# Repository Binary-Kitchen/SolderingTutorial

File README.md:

# Soldering Tutorial

This repository contains all files for our soldering kits and courses. Please feel free to download and use everything you need.

We've tried to collect and create tutorials with different difficulties and are offering SMD and DIP soldering kits.

For an overview of all kits with manuals and interactive pcb views go to: https://binary-kitchen.github.io/SolderingTutorial

### Linking directly to a kit

Every kit on the overview page has its own anchor, so you can link straight to its picture:
`https://binary-kitchen.github.io/SolderingTutorial/#Capybara` opens the page scrolled to the Capybara card and highlights it.
Clicking the small link icon on a card copies that deep link to your clipboard.

The overview page is generated from the project folders — `make landing_page`, i.e. `python build_landingpage.py`.
Every folder that contains a card image at `manual/images/thumbnail.{jpg,jpeg,png,gif,webp}` shows up automatically,
so a new kit only needs such a thumbnail to appear on the page.

If you want to buy soldering Kits you can find some here: [shop.blinkyparts.com](https://shop.blinkyparts.com)

We have tips how to organise a soldering workshop in the field and how to further decorate the kits: [Wiki: Festival Setup](https://github.com/Binary-Kitchen/SolderingTutorial/wiki/Festival-Setup)

## Soldering Kits

### [50 Ohm Dummy Load](50ohmDummyLoad/)

A simple Dummy Load for 50 Ohm made for every amateur radio operator.

- Difficulty: **§/5**

### [Atari Punk Console - STEAM Edition](AtariPunkConsoleSTEAM/)

One of the simplestes Synthesizers you can build. Only two NE555 make super cool sounds!

- Difficulty: **1/5**

### [ATX Breakout Board](ATXBreakoutBoardSMD/)

Handy Breakout Board to get all the important voltages from a standard ATX power supply.

- Difficulty: **4/5**

### [Al Hacka Alpaka](AlHackaAlpaka/)

Easy soldering kit in homage to Jugend hackt and its mascot.

### [Arrow SMD](ArrowSMD/)

Small soldering kit with an arrow on it from https://wiki.blinkenarea.org/index.php/AntiKippenLights-Mini.

- Difficulty: **4/5**

### [Axolotl Badge](AxolotlBadge/)

Easy RGB soldering kit with the best Axolotl!

- Difficulty: **2/5**

### [BleepBot](BleepBot/)

A talking robot!

- Difficulty: **2/5**

### [Blinkenrocket Mini](BlinkenrocketMini/)

A very simple soldering kit and a very intuitive way to program your own led matrix. Super fun blinkenrocket!

- Difficulty: **2/5**

### [BlinkyTree](BlinkyTree/)

The BlinkyTree is a soldering kit for a fantastic soldering Christmas tree. The great feature: By blowing on the tree, you can play different songs. A wonderful soldering kit for the Christmas season.

- Difficulty: **2/5**

### [Pooping Cat](PoopingCat/)

Can you please turn around? If you stare, the cat will stare back in all colours of the rainbow due to RGB-LEDs on the back. The soldering kit is very simple and easy to assemble.

- Difficulty: **2/5**

### [Cube DIP](CubeDIP/)

Simple LED cube consisting of 27 RGB LEDs in a 3x3x3 configuration. No programming needed.

- Difficulty: **3/5**

### [Daisy RGB](Daisy_RGB/)

This 3D construction kit allows you to solder a personalized daisy with a large RGB LED in the center, with colors adjustable using variable resistors and overall brightness and individual colors adjustable via slide switches.

- Difficulty: **2/5**

### [Dice DIP](DiceDIP/)

Electronic dice which uses button bouncing and timing for randomness.

- Difficulty: **3/5**

### [Dice Micro Controller DIP](DiceMcDIP/)

Dice with micro controller. Electronic dice which uses C random generator.

- Difficulty: **2/5**

### [Dino](Dino/)

This rainbow dinosaur will brighten up your life. The spikes are glowing in all colours of the rainbow due to RGB-LEDs on the back. The soldering kit is very simple and easy to assemble.

- Difficulty: **2/5**

### [Draussenfuchs Antenna](DraussenfuchsAntenne/)

A soldering kit for a simple 433MHz Yagi antenna designed for the draussenfuchs.de fox hunting game.

- Difficulty: **2/5**

### [Draussenfuchs Sender](DraussenfuchsSender/)

A soldering kit for a 433MHz fox sender for the draussenfuchs.de fox hunting game.

- Difficulty: **2/5**

### [Elefant](Elefant/)

Everyone knows the great elephant from the “Sendung mit der Maus” and, as always, he has a good idea. An LED in the trunk that lights up in RGB colors.

- Difficulty: **2/5**

### [Ermer Beeper DIP](ErmerBeeperDIP/)

The Ermer Beeper is a very neat continuity tester or beeper.

- Difficulty: **2/5**

### [Heartbeat](HeartbeatTHT/)

Small soldering kit with an heart and a beating led in the middle.

- Difficulty: **2/5**

### [Heart DIP](HeartDIP/)

Small soldering kit with an heart on from https://wiki.blinkenarea.org/index.php/AntiKippenLights-Atmel

- Difficulty: **2/5**

### [Heart SMD](HeartSMD/)

Small soldering kit with an heart on it from https://wiki.blinkenarea.org/index.php/AKL-Mini

- Difficulty: **4/5**

### [Humo - Solder-Fume Exctractor](Humo/)

This simple solder fume extractor just needs a PC fan and a solder fume filter. If you add some goggly eyes the fume extractor has a pretty nice smiling face. It is optimised for laser cut parts.

- Difficulty: **2/5**

### [I Can Solder DIP](ICanSolderDIP/)

Very easy soldering kit with three LEDs. Can be used as pin button.

- Difficulty: **1/5**

### [Katie The Cat](KatieTheCat/)

A wonderful and easy soldering Kit with two different eye-colours.

- Difficulty: **2/5**

### [Kitchen Head SMD](KitchenHeadSMD/)

Small soldering kit using SMD components with the kitchen head on it.

- Difficulty: **4/5**

### [LEDSchmuck](LEDSchmuck/)

The LED jewelry kit allows you to easily and quickly assemble earrings or pendants with RGB LEDs. It's a creative kit for making great individual jewelry pieces.

- Difficulty: **2/5**

### [LEDWolf](LEDWolf/)

This great LED wolf is a good way to start tinkering if you don't have a soldering iron with you at the moment. All you need is a little glue and a small Phillips screwdriver to assemble this great wolf.

- Difficulty: **1/5**

### [Maus](Maus/)

An easy hot wire soldering kit with the Sendung mit der Maus.

### [Moon Cat](MoonCat/)

Excuse me? What are you staring at? This wonderful kit is very simple in terms of circuitry, but the result is simply hilarious.

- Difficulty: **2/5**

### [Motörbörd](MotoerBoerd/)

Chirp chirp chirp, chirp chirp! The Motörbörd is a creative soldering kit that you can use to build your own little bird call generator. It is not powered by batteries, but by a small motor that generates electrical energy when turned like a dynamo.

- Difficulty: **2/5**

### [Mushroom Rocket](https://github.com/ventilator/soldering-mushroom-rocket/tree/main)

A fusion between a rocket and a mushroom

- Difficulty: **2/5**

### [NE555 Heart THT](NE555HeartTHT/)

A wonderful Heart with SMD LEDs. You can choose between full on, follow-LEDs and even can influence the speed of your LEDs.

- Difficulty: **3/5**

### [NE555 Heart SMD](NE555HeartSMD/)

A wonderful Heart with SMD LEDs. You can choose between full on, follow-LEDs and even can influence the speed of your LEDs.

- Difficulty: **4/5**

### [Nibble++](NibblePlusPlusSMD/)

A simple PCB to test your SMD hand-soldering skills. Going down to sand grain sized 01005 SMD parts, this button is a challenge for experienced "soldiers" and those who want to become one.

- Difficulty: **6/5**

### Nibble Peg DIP

#### [Nibble Peg DIP](NibblePegDIP/)

Very easy soldering Kit using simple Tools and nearly no soldering knowledge is needed.

- Difficulty: **1/5**

#### [Nibble Peg DIP with On/Off Switch](NibblePegDIPSwitch/)

Easy soldering Kit using simple Tools and nearly no soldering knowledge is needed.

- Difficulty: **2/5**

### [Nose Dog](NoseDog/)

Easy soldering Kit using simple Tools and nearly no soldering knowledge is needed.

- Difficulty: **2/5**

### [OpenDTU Breakout Board](OpenDTU_Breakout/)

A board to get information from your solar power panels with an Hoymiles inverter.

- Difficulty: **2/5**

### [Owl Thief THT](OwlThiefDIP/)

A simple joule thief circuit on the back of an owl. If you solder everything right, you can empty old batteries and make the eyes glow orange.

- Difficulty: **2/5**

### [Pinecil Case](Pinecil_Case/)

A perfect 3D-printed rugged case for your pinecil, extra tips and usb-c cable.

- Difficulty: **1/5**

### [Push-It DIP](PushItDIP/)

Simon Says clone with (optional) multiplayer mode

- Difficulty: **2/5**

### [Rainbow Butterfly](RainbowButterfly/)

A wonderful rainbow Butterfly. The wings are enlighted by RGB-LEDs from the back of the PCB. The soldering kit is very simple and easy to assemble.

- Difficulty: **2/5**

### [Rainbow Unicorn 1](RainbowUnicorn01/)

This unicorn will brighten up your life. The hair is glowing in all colours of the rainbow due to RGB-LEDs on the back. The soldering kit is very simple and easy to assemble.

- Difficulty: **2/5**

### [Ring Light SMD](RingLightSMD/)

A simple SMD learning kit where a light chases around a circle.

- Difficulty: **4/5**

### [Robo Robin](RoboRobin/)

Light up this super easy Robot. It has RGB-LEDs as eyes.

- Difficulty: **1/5**

### [Rainbow Rocket](RocketBadge/)

Fly to the moon with this RGB rocket badge.

- Difficulty: **2/5**

### [Saw-Tooth Organ DIP](SawToothOrganDIP/)

Some Transistors creating a saw tooth wave enabling a very simple organ which you can play like a piano with a stylus.

- Difficulty: **2/5**

### [Shitty Robot](ShittyRobots/)

A very easy circuit to power a little robot with a vibration motor.

- Difficulty: **1/5**

### [SmartLED](SmartLED/)

Create a wonderful smart LED-Lamp you can control with you Smartphone.

- Difficulty: **4/5**

### [Smartphone Robot](SmartphoneRobot/)

A robot made out of an old smartphone. You can controll it by turning light on and off.

- Difficulty: **2/5**

### [SMD Cat](SMDCat/)

A Cat in a box easy SMD kit. Bright glowing LED-eyes are watching every step! With this soldering kit it is super easy to learn SMD soldering.

- Difficulty: **3/5**

### [Solarpunk Synthesizer](SolarpunkSynth/)

A very simple solarpunk Synthesizer based on a simple Schmitt Trigger. Create crazy sounds with this simple soldering kit.

- Difficulty: **2/5**

### [SolderBox](SolderBox/)

We have designed a soldering box for you that is extra small but still contains everything you need. The box offers space for a complete soldering working place and is still so small that four of the boxes fit into a small Euro box.

- Difficulty: **1/5**

### [SpaceEggs](SpaceEggs/)

The **Space Egg** is a fun and beginner-friendly **soldering kit** combined with **3D-printed components**. It features an interactive mechanism where turning the egg

- Difficulty: **2/5**

### [WeevilEye](WeevilEye/)

The kit is a very easy kit with push-through parts, which is explicitly aimed at beginners. Once assembled, the red LED “eyes” light up brighter or dimmer depending on how much light falls on the photo sensor.

- Difficulty: **2/5**

## License

This work is licensed under different licenses. Please see subfolders for details and LICENSE.md file in the top level directory for all used license files.

## Copyright and Authorship

Please consider README.md in sub-folders for the Copyright and Authorship of the specific project.

## Authors

Boards:

- Arne Rossius [arne@blinkenarea.org](mailto:arne@blinkenarea.org)
- Thomas Basler [noby@binary-kitchen.de](mailto:noby@binary-kitchen.de)
- Francesco Truzzi <http://truzzi.me>
- Timo Schindler <https://www.timoschindler.de>
- Thomas Schmid

TeX-Code:

- Marei Peischl [marei@binary-kitchen.de](mailto:marei@binary-kitchen.de) <https://github.com/TeXhackse>

Comic:

- Mitch Altmann <http://cornfieldelectronics.com>
- Jeff Keyzer <http://mightyohm.com/blog/>
- Andie Nordgren [andie.nordgren@gmail.com](mailto:andie.nordgren@gmail.com)

Manuals:

- Michael Pajewski
- Marei Peischl [marei@binary-kitchen.de](mailto:marei@binary-kitchen.de) <https://github.com/TeXhackse>
- Timo Schindler <https://www.timoschindler.de>
- Hannes <https://github.com/misamura>
- Mario Langhammer <https://github.com/Mallo321123>

Note: This list of authors can be incomplete. Please also consider the README.md in the sub-folders for authorship.

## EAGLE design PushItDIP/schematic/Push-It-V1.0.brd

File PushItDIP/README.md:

# Push-It DIP
Simon Says clone with (optional) multiplayer mode

- Status: **Complete**
- Difficulty: **2/5**

### Parts List

| Quantity | Name        | Description                        | Signing/Colorcode             |
|----------|-------------|------------------------------------|-------------------------------|
| 5        | R1 - R4, R6 | Resistor 220 Ohm                   | red - red - brown - gold      |
| 1        | R5          | Resistor 1 Kilo Ohm                | brown - black - red - gold    |
| 1        | R7          | Resistor 10 Kilo Ohm               | brown - black - orange - gold |
| 7        | S1 - S7     | Button                             |                               |
| 1        | SG1         | Speaker                            |                               |
| 1        | JP1         | Pinheader 3x1                      |                               |
| 1        | LED1        | LED 10mm Yellow                    |                               |
| 1        | LED2        | LED 10mm Red                       |                               |
| 1        | LED3        | LED 10mm Green                     |                               |
| 1        | LED4        | LED 10mm Blue                      |                               |
| 1        | LED7        | 7-Segment Display (SA39-11SRWA)    |                               |
| 2        | C1, C2      | Ceramic capacitor 100 nF           | 104                           |
| 2        | C3, C4      | Ceramic capacitor 22 pF            | 22                            |
| 1        | IC1         | 74HC 595                           |                               |
| 1        | IC2         | Mikrocontroller Atmel Atmega 328P  |                               |
| 1        | Q1          | 16MHz Oscillator                   |                               |
| 1        | POWER       | Screw TConnector 2-pin             |                               |
| 1        |             | IC-Socket 16-pin                   |                               |
| 1        |             | IC-Socket 28-pin                   |                               |
| 1        |             | Circuit Board (PCB)                |                               |
| 1        |             | Battery Case                       |                               |
| 4        |             | Battery Mignon (AA)                |                               |

### Manual
You can find the manual and pictures of every step in the manual folder.

### Copyright and Authorship
- Board: [CC-BY-SA 4.0](https://creativecommons.org/licenses/by-sa/4.0/) - Thomas Basler
- Manual (TeX): [LPPL](https://www.latex-project.org/lppl.txt) - [Marei Peischl](https://peitex.de)
- Manual (pdf): [CC-BY-SA 4.0](https://creativecommons.org/licenses/by-sa/4.0/) - [Binary Kitchen e.V.](https://www.binary-kitchen.de)

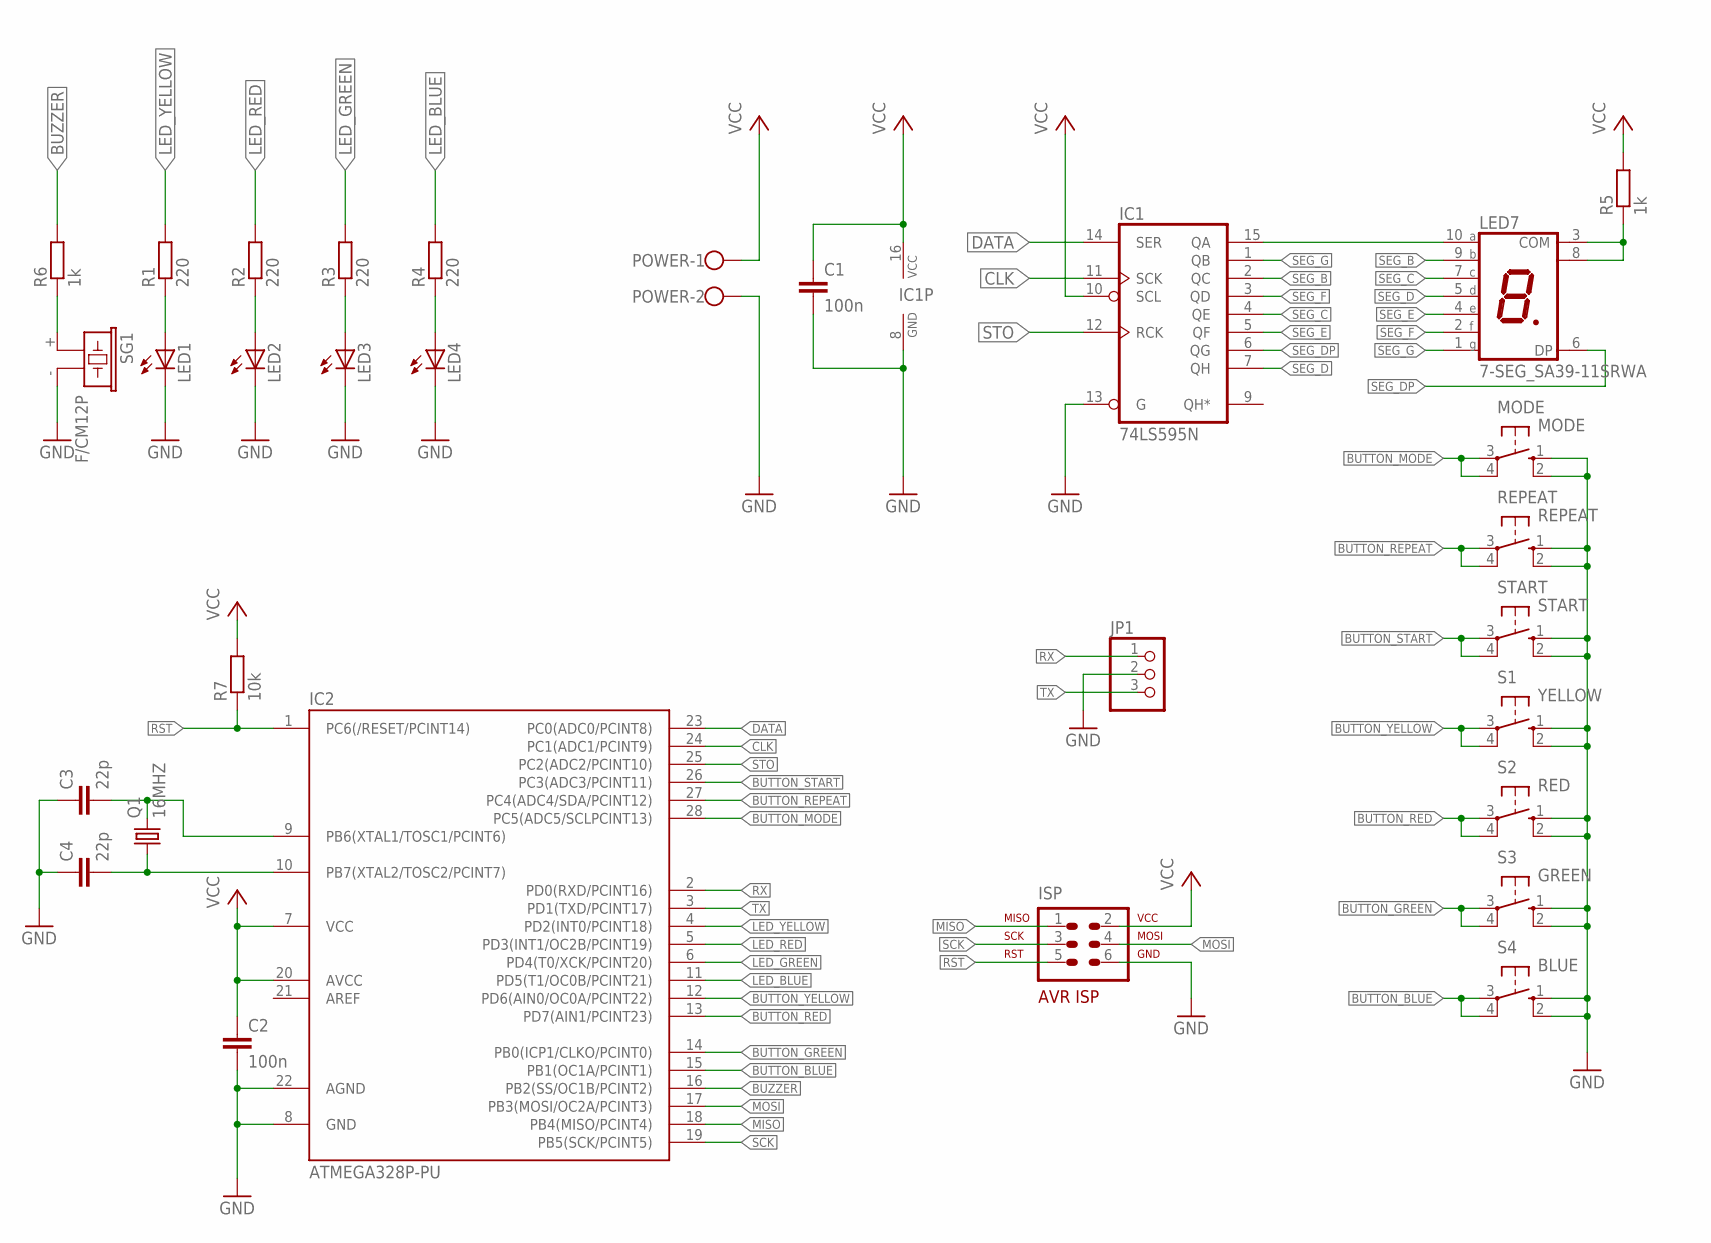
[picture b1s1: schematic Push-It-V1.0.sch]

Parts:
C1, C2: 100n; C025-025X050
C3, C4: 22p; C025-025X050
IC1: 74LS595N; DIL16
IC2: ATMEGA328P-PU; DIL28-3
ISP: AVR-ISP-6VERT; AVR-ISP-6
JP1: PINHD-1X3/90; 1X03/90
LED1, LED2, LED3, LED4: LED10MM
LED7: 7-SEG_SA39-11SRWA; SA39-11SRWA
MODE: MODE; B3F-10XX
POWER: W237-102
Q1: 16MHZ; HC49/S
R1, R2, R3, R4: 220; 0207/7
R5, R6: 1k; 0207/7
R7: 10k; 0207/7
REPEAT: REPEAT; B3F-10XX
S1: YELLOW; B3F-10XX
S2: RED; B3F-10XX
S3: GREEN; B3F-10XX
S4: BLUE; B3F-10XX
SG1: F/CM12P
START: START; B3F-10XX

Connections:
BUTTON_BLUE: IC2.15 (PB1(OC1A/PCINT1)), S4.3, S4.4 (P1)
BUTTON_GREEN: IC2.14 (PB0(ICP1/CLKO/PCINT0)), S3.3, S3.4 (P1)
BUTTON_MODE: IC2.28 (PC5(ADC5/SCLPCINT13)), MODE.3, MODE.4 (P1)
BUTTON_RED: IC2.13 (PD7(AIN1/PCINT23)), S2.3, S2.4 (P1)
BUTTON_REPEAT: IC2.27 (PC4(ADC4/SDA/PCINT12)), REPEAT.3, REPEAT.4 (P1)
BUTTON_START: IC2.26 (PC3(ADC3/PCINT11)), START.3, START.4 (P1)
BUTTON_YELLOW: IC2.12 (PD6(AIN0/OC0A/PCINT22)), S1.3, S1.4 (P1)
BUZZER: IC2.16 (PB2(SS/OC1B/PCINT2)), R6.2
CLK: IC1.11 (SCK), IC2.24 (PC1(ADC1/PCINT9))
DATA: IC1.14 (SER), IC2.23 (PC0(ADC0/PCINT8))
GND: C1.2, C2.2, C3.1, C4.1, IC1.8 (GND), IC1.13 (G), IC2.8 (GND), IC2.22 (AGND), ISP.6, JP1.2, LED1.K (C), LED2.K (C), LED3.K (C), LED4.K (C), MODE.1 (S), MODE.2 (S1), POWER.2, REPEAT.1 (S), REPEAT.2 (S1), S1.1 (S), S1.2 (S1), S2.1 (S), S2.2 (S1), S3.1 (S), S3.2 (S1), S4.1 (S), S4.2 (S1), SG1.- (2), START.1 (S), START.2 (S1)
LED_BLUE: IC2.11 (PD5(T1/OC0B/PCINT21)), R4.2
LED_GREEN: IC2.6 (PD4(T0/XCK/PCINT20)), R3.2
LED_RED: IC2.5 (PD3(INT1/OC2B/PCINT19)), R2.2
LED_YELLOW: IC2.4 (PD2(INT0/PCINT18)), R1.2
MISO: IC2.18 (PB4(MISO/PCINT4)), ISP.1
MOSI: IC2.17 (PB3(MOSI/OC2A/PCINT3)), ISP.4
unnamed: LED1.A, R1.1
unnamed: LED2.A, R2.1
unnamed: LED3.A, R3.1
unnamed: LED4.A, R4.1
unnamed: IC1.15 (QA), LED7.10 (A)
unnamed: LED7.3 (COM), LED7.8 (COM), R5.1
unnamed: C4.2, IC2.10 (PB7(XTAL2/TOSC2/PCINT7)), Q1.1
unnamed: C3.2, IC2.9 (PB6(XTAL1/TOSC1/PCINT6)), Q1.2
unnamed: R6.1, SG1.+ (1)
RST: IC2.1 (PC6(/RESET/PCINT14)), ISP.5, R7.1
RX: IC2.2 (PD0(RXD/PCINT16)), JP1.1
SCK: IC2.19 (PB5(SCK/PCINT5)), ISP.3
SEG_B: IC1.2 (QC), LED7.9 (B)
SEG_C: IC1.4 (QE), LED7.7 (C)
SEG_D: IC1.7 (QH), LED7.5 (D)
SEG_DP: IC1.6 (QG), LED7.6 (DP)
SEG_E: IC1.5 (QF), LED7.4 (E)
SEG_F: IC1.3 (QD), LED7.2 (F)
SEG_G: IC1.1 (QB), LED7.1 (G)
STO: IC1.12 (RCK), IC2.25 (PC2(ADC2/PCINT10))
TX: IC2.3 (PD1(TXD/PCINT17)), JP1.3
VCC: C1.1, C2.1, IC1.10 (SCL), IC1.16 (VCC), IC2.7 (VCC), IC2.20 (AVCC), ISP.2, POWER.1, R5.2, R7.2

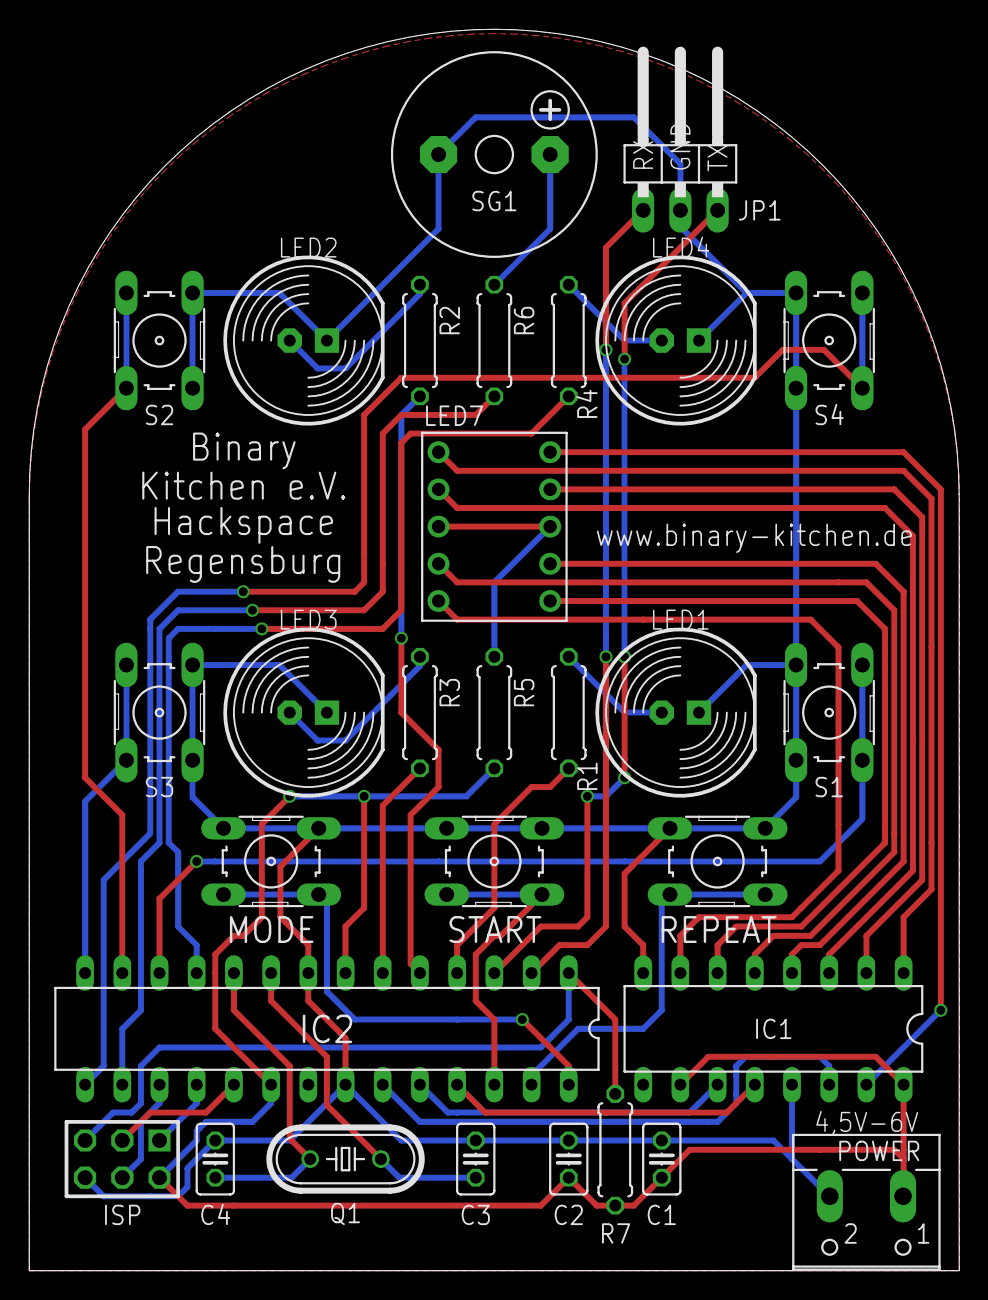
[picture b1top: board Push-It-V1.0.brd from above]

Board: 2 copper layers, 63.5 x 84.8 mm, 30 parts (0 on the bottom side), 39 nets.

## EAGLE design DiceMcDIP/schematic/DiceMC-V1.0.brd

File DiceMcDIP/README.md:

# Dice Microcontroller - DIP
Electronic dice with Microcontroller and less parts.

- Status: **Complete**
- Difficulty: **2/5**

### Parts List

| Menge | Name            | Beschreibung                       | Beschriftung/Farbcode |
|-------|-----------------|------------------------------------|-----------------------|
| 1     | C1              | Keramik Kondensator 100nF          |                       |
| 1     | IC1             | Mikrocontroller Atmel ATTiny 2313A |                       |
| 7     | LED1 - LED7     | 5mm LED                            |                       |
| 7     | R1 - R7         | Widerstand 82 Ohm                  | 470                   |
| 1     | S1              | Taster                             |                       |
| 1     | X1              | Klemme 2-polig                     |                       |
| 1     |                 | IC-Sockel 20-polig                 |                       |
| 1     |                 | Batteriehalter                     |                       |
| 2     |                 | Batterie Mignon (AA)               |                       |
| 1     |                 | Platine                            |                       |

### Manual
You can find the manual and pictures of every step in the manual folder.

### Copyright and Authorship
- Board: [CC-BY-SA 4.0](https://creativecommons.org/licenses/by-sa/4.0/) - Thomas Basler
- Manual (TeX): [LPPL](https://www.latex-project.org/lppl.txt) - [Marei Peischl](https://peitex.de)
- Manual (pdf): [CC-BY-SA 4.0](https://creativecommons.org/licenses/by-sa/4.0/) - [Binary Kitchen e.V.](https://www.binary-kitchen.de)

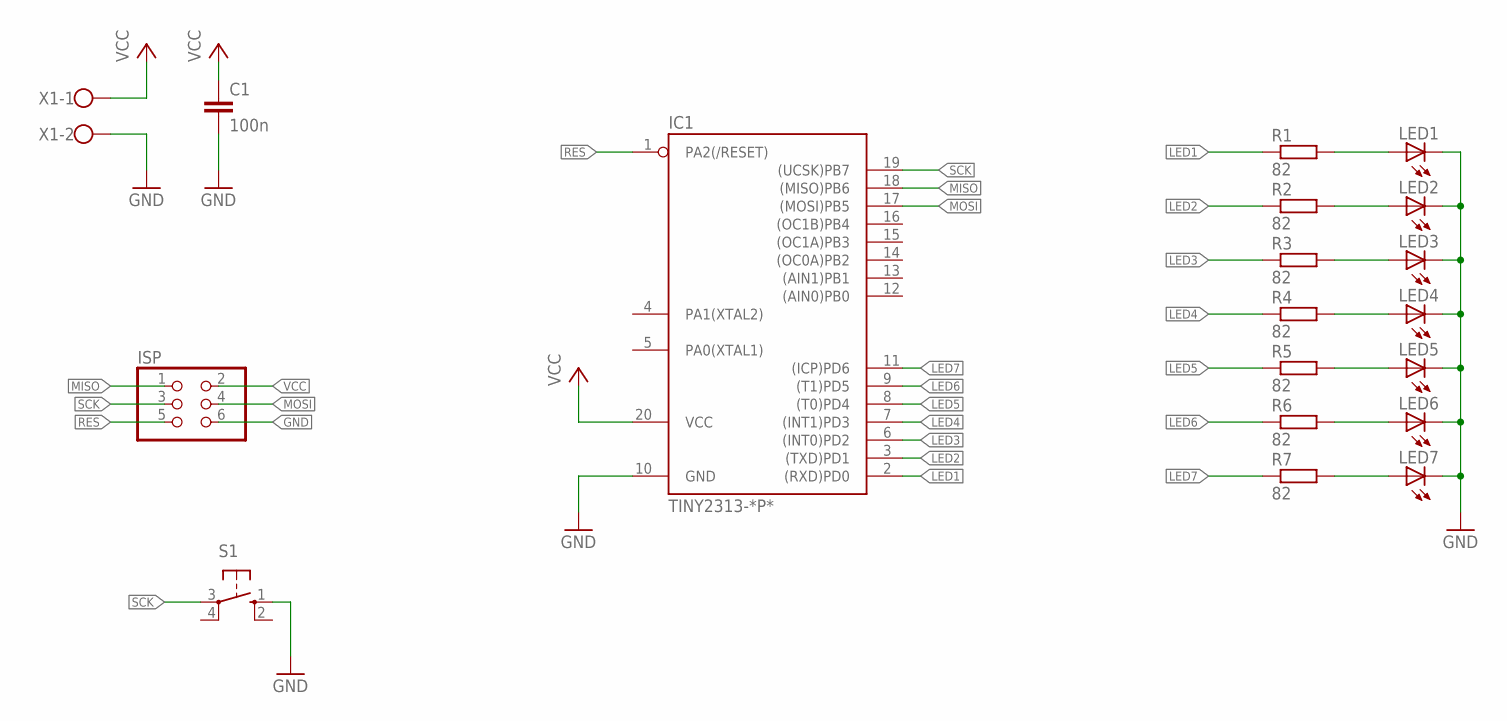
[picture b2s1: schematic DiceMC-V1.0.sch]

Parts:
C1: 100n; C025-025X050
IC1: TINY2313-*P*; DIL20
ISP: PINHD-2X03_2.54; 2X03
LED1, LED2, LED3, LED4, LED5, LED6, LED7: LED5MM
R1, R2, R3, R4, R5, R6, R7: 82; 0207/7
S1: 10-XX; B3F-10XX
X1: W237-102

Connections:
GND: C1.2, IC1.10 (GND), ISP.6, LED1.K (C), LED2.K (C), LED3.K (C), LED4.K (C), LED5.K (C), LED6.K (C), LED7.K (C), S1.1 (S), X1.2
LED1: IC1.2 ((RXD)PD0), R1.1
LED2: IC1.3 ((TXD)PD1), R2.1
LED3: IC1.6 ((INT0)PD2), R3.1
LED4: IC1.7 ((INT1)PD3), R4.1
LED5: IC1.8 ((T0)PD4), R5.1
LED6: IC1.9 ((T1)PD5), R6.1
LED7: IC1.11 ((ICP)PD6), R7.1
MISO: IC1.18 ((MISO)PB6), ISP.1
MOSI: IC1.17 ((MOSI)PB5), ISP.4
unnamed: LED1.A, R1.2
unnamed: LED2.A, R2.2
unnamed: LED3.A, R3.2
unnamed: LED4.A, R4.2
unnamed: LED5.A, R5.2
unnamed: LED6.A, R6.2
unnamed: LED7.A, R7.2
RES: IC1.1 (PA2(/RESET)), ISP.5
SCK: IC1.19 ((UCSK)PB7), ISP.3, S1.3
VCC: C1.1, IC1.20 (VCC), ISP.2, X1.1

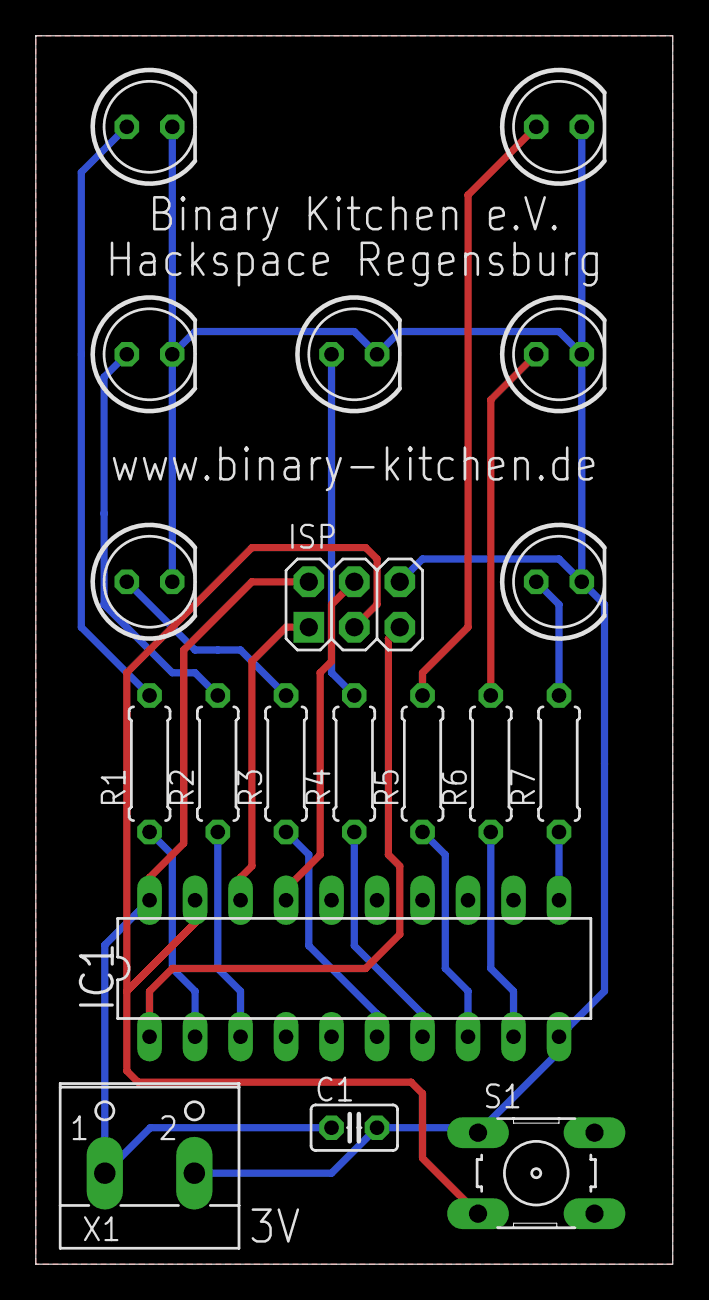
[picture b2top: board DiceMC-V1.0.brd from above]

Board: 2 copper layers, 35.6 x 68.6 mm, 19 parts (0 on the bottom side), 20 nets.

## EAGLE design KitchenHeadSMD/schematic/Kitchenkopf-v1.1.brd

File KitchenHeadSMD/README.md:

# KitchenHead - SMD
Small soldering kit using SMD components with the kitchen head on it.

- Status: **Complete**
- Difficulty: **4/5**

### Parts List

| Menge | Name            | Beschreibung                       | Beschriftung/Farbcode |
|-------|-----------------|------------------------------------|-----------------------|
| 1     | C2              | Keramik Kondensator 100nF          |                       |
| 1     | IC1             | Mikrocontroller Atmel ATTiny 2313A |                       |
| 21    | LED1 - LED21    | LED SMD 0805                       |                       |
| 7     | R2 - R8         | Widerstand 47 Ohm                  | 470                   |
| 1     | SW1             | Taster                             |                       |
| 1     | BAT1            | Batteriehalter                     |                       |
| 1     |                 | Batterie CR2032                    |                       |
| 1     |                 | Platine                            |                       |

### Manual
You can find the manual and pictures of every step in the manual folder.

### Copyright and Authorship
The project is based on http://wiki.blinkenarea.org/index.php/AntiKippenLights-Mini

- Board: [CC-BY-NC-SA 4.0](https://creativecommons.org/licenses/by-nc-sa/4.0/) - Arne Rossius, Thomas Basler
- Manual (TeX): [LPPL](https://www.latex-project.org/lppl.txt) - [Marei Peischl](https://peitex.de)
- Manual (pdf): [CC-BY-SA 4.0](https://creativecommons.org/licenses/by-sa/4.0/) - [Binary Kitchen e.V.](https://www.binary-kitchen.de)

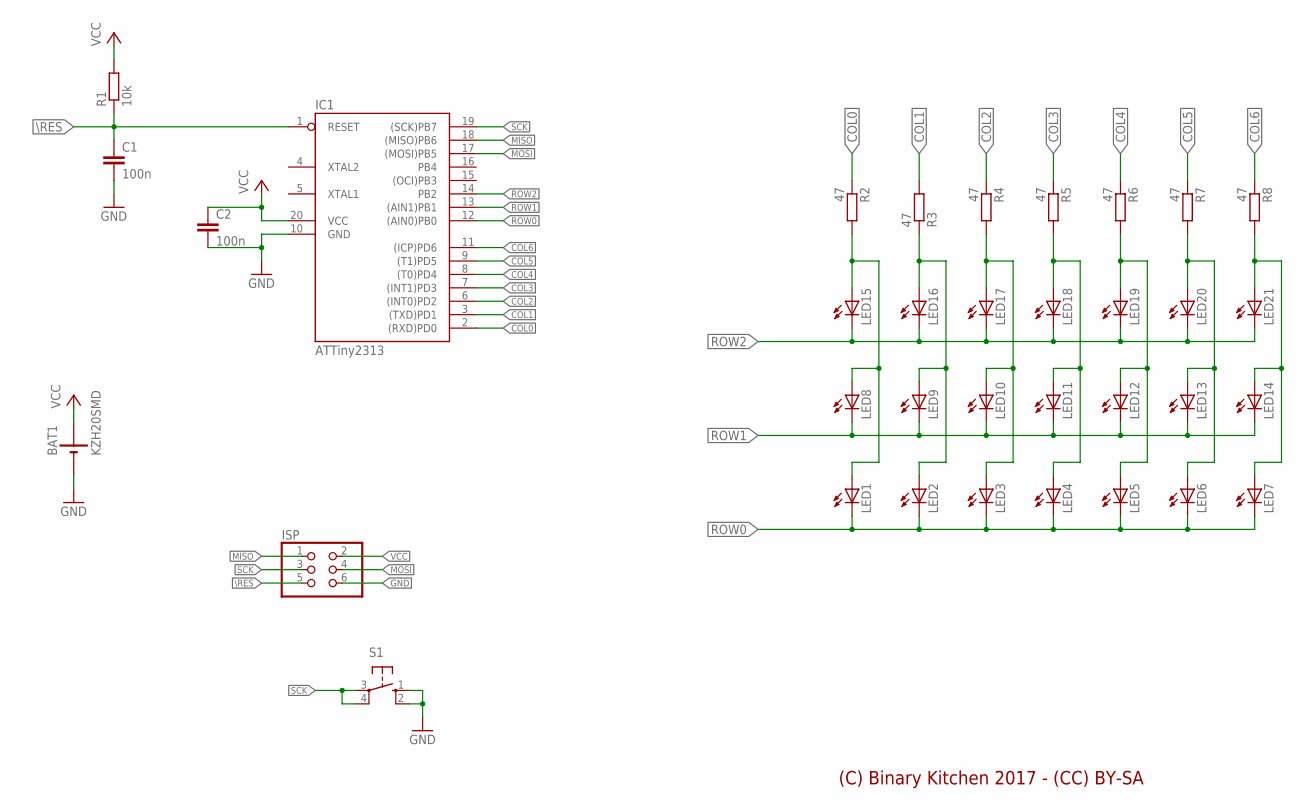
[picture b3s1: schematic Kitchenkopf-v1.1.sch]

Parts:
BAT1: KZH20SMD
C1, C2: 100n; C0805
IC1: ATTiny2313; SO20L
ISP: PINHD-2X03_2.54; 2X03
LED1, LED2, LED3, LED4, LED5, LED6, LED7, LED8, LED9, LED10, LED11, LED12, LED13, LED14, LED15, LED16, LED17, LED18, LED19, LED20, LED21: LEDCHIP-LED0805; CHIP-LED0805
R1: 10k; R0805
R2, R3, R4, R5, R6, R7, R8: 47; R0805
S1: 10-XX; B3F-10XX

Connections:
COL0: IC1.2 ((RXD)PD0), R2.1
COL1: IC1.3 ((TXD)PD1), R3.2
COL2: IC1.6 ((INT0)PD2), R4.1
COL3: IC1.7 ((INT1)PD3), R5.1
COL4: IC1.8 ((T0)PD4), R6.1
COL5: IC1.9 ((T1)PD5), R7.1
COL6: IC1.11 ((ICP)PD6), R8.1
GND: BAT1.NEG (-), C1.2, C2.2, IC1.10 (GND), ISP.6, S1.1 (S), S1.2 (S1)
MISO: IC1.18 ((MISO)PB6), ISP.1
MOSI: IC1.17 ((MOSI)PB5), ISP.4
unnamed: LED1.A, LED8.A, LED15.A, R2.2
unnamed: LED2.A, LED9.A, LED16.A, R3.1
unnamed: LED3.A, LED10.A, LED17.A, R4.2
unnamed: LED4.A, LED11.A, LED18.A, R5.2
unnamed: LED5.A, LED12.A, LED19.A, R6.2
unnamed: LED6.A, LED13.A, LED20.A, R7.2
unnamed: LED7.A, LED14.A, LED21.A, R8.2
ROW0: IC1.12 ((AIN0)PB0), LED1.C, LED2.C, LED3.C, LED4.C, LED5.C, LED6.C, LED7.C
ROW1: IC1.13 ((AIN1)PB1), LED8.C, LED9.C, LED10.C, LED11.C, LED12.C, LED13.C, LED14.C
ROW2: IC1.14 (PB2), LED15.C, LED16.C, LED17.C, LED18.C, LED19.C, LED20.C, LED21.C
SCK: IC1.19 ((SCK)PB7), ISP.3, S1.3, S1.4 (P1)
VCC: BAT1.POS (+), C2.1, IC1.20 (VCC), ISP.2, R1.2
\RES: C1.1, IC1.1 (RESET), ISP.5, R1.1

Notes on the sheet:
(C) Binary Kitchen 2017 - (CC) BY-SA

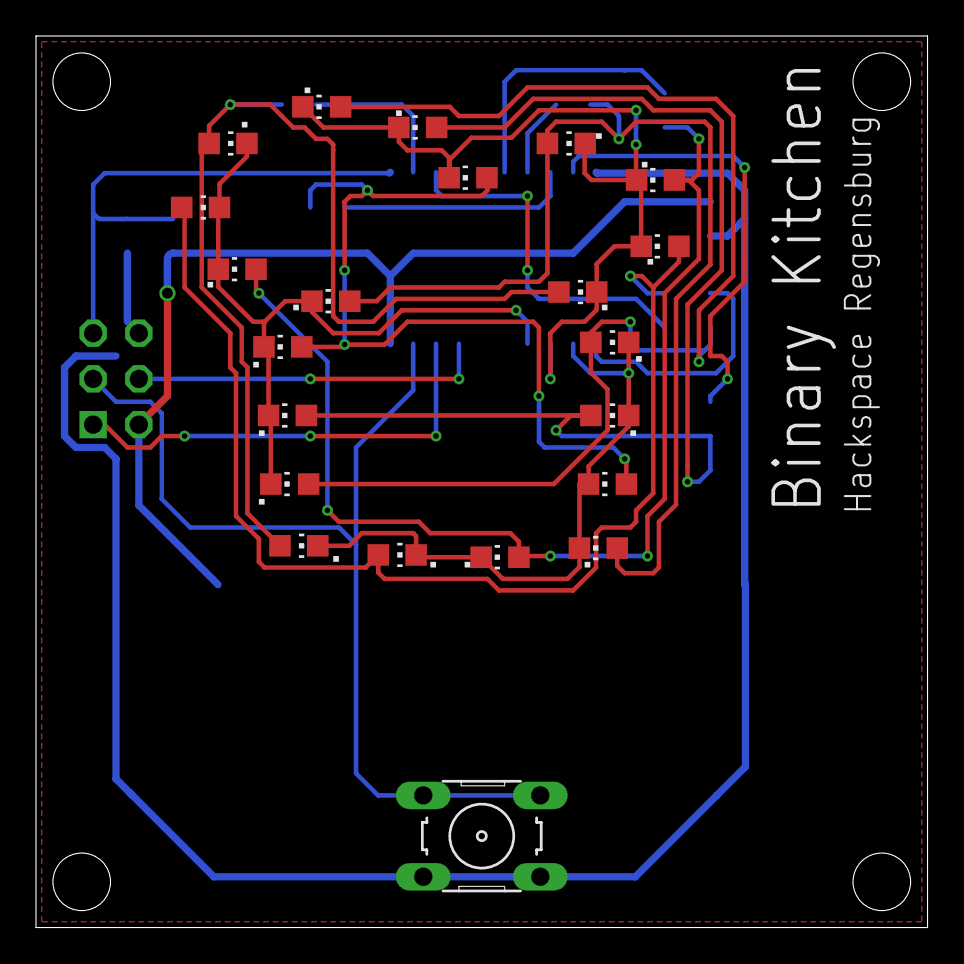
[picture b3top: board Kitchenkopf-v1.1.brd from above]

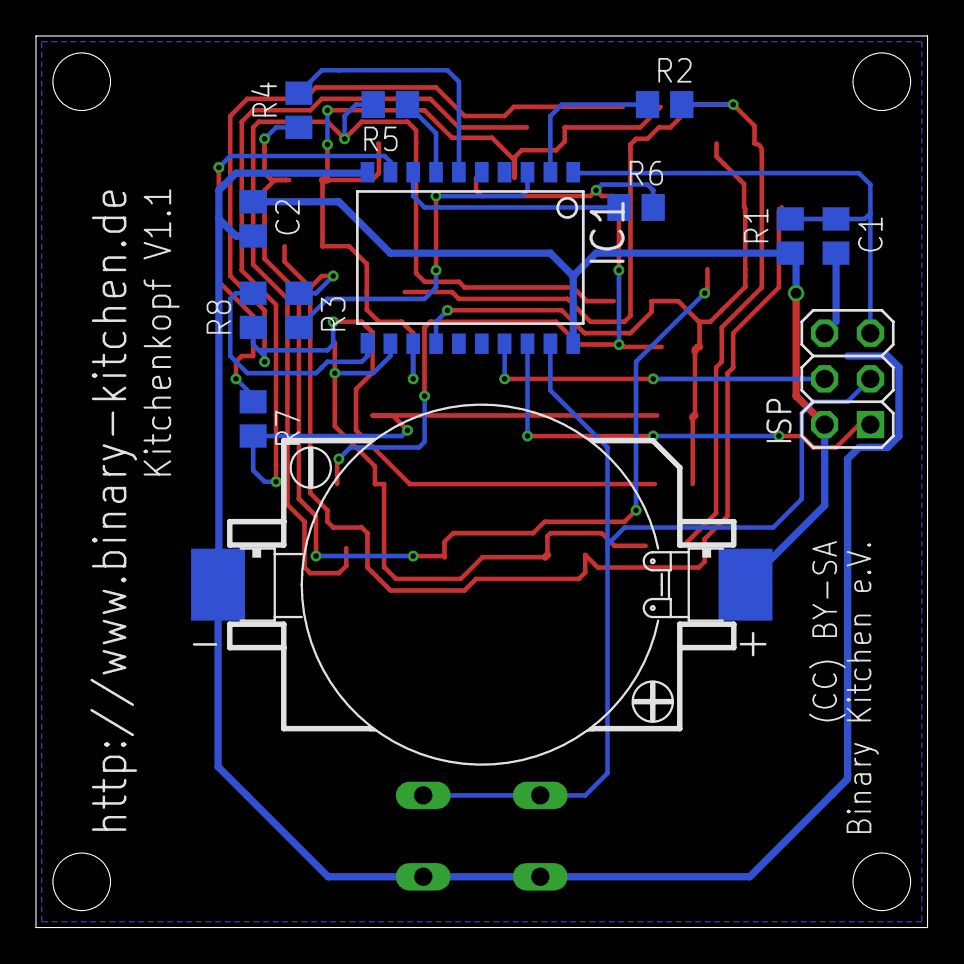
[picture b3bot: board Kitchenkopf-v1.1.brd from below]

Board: 2 copper layers, 49.5 x 49.5 mm, 35 parts (13 on the bottom side), 23 nets.

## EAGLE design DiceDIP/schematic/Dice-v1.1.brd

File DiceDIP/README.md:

# Dice DIP
Electronic dice which uses button bouncing and timing for randomness.

- Status: **Complete**
- Difficulty: **4/5**

### Parts List
| Quantity | Name                          | Description                | Signing/Colorcode                         |
|----------|-------------------------------|----------------------------|-------------------------------------------|
| 2        | C1, C2                        | Ceramic capacitor 100 nF   | 104                                       |
| 1        | C3                            | Capacitor 47uF             |                                           |
| 3        | D1, D2, D3                    | Diode BAW 76               |                                           |
| 1        | D10                           | Diode 1N4007               |                                           |
| 1        | IC1                           | CMOS-IC 4029               |                                           |
| 1        | IC2                           | CMOS-IC 4093               |                                           |
| 7        | LED1 -- LED7                  | LED 5 mm                   |                                           |
| 2        | R1, R3                        | Resistor 2,2k Ohm          | red - red - black - brown - brown         |
| 1        | R2                            | Resistor 1M Ohm            | brown - black - black - yellow - brown    |
| 1        | R4                            | Resistor 2,2M Ohm          | red - red - black - yellow - brown        |
| 1        | R5                            | Resistor 120k Ohm          | brown - red - black - orange - brown      |
| 2        | R6, R8                        | Resistor 1,5k Ohm          | brown - green - black - brown - brown     |
| 1        | R7                            | Resistor 1,8k Ohm          | brown - gray - black - brown - brown      |
| 1        | R9                            | Resistor 3,3k Ohm          | orange - orange - black - brown - brown   |
| 1        | T1                            | Transistor BC547B          |                                           |
| 1        | S1                            | Button                     |                                           |
| 1        | X1                            | USB female connector      	|                                           |
| 1        | PCB / circuit board           |                            |                                           |
| 1        | IC-socket 14-polig            |                            |                                           |
| 1        | IC-socket 16-polig            |                            |                                           |
| 1        | Batteryclip für 9-Volt-Block  |                            |                                           |
| 1        | Battery 9V Block              |                            |                                           |

### Manual
You can find the manual and pictures of every step in the manual folder.

### Copyright and Authorship
The project is based on https://www.ei.rub.de/media/ei/attachments/files/2009/12/Dokumentation_elektronischer_Wuerfel.pdf

- Board: [CC-BY-SA 4.0](https://creativecommons.org/licenses/by-sa/4.0/) - Thomas Basler
- Manual (TeX): [LPPL](https://www.latex-project.org/lppl.txt) - [Marei Peischl](https://peitex.de)
- Manual (pdf): [CC-BY-SA 4.0](https://creativecommons.org/licenses/by-sa/4.0/) - [Binary Kitchen e.V.](https://www.binary-kitchen.de)

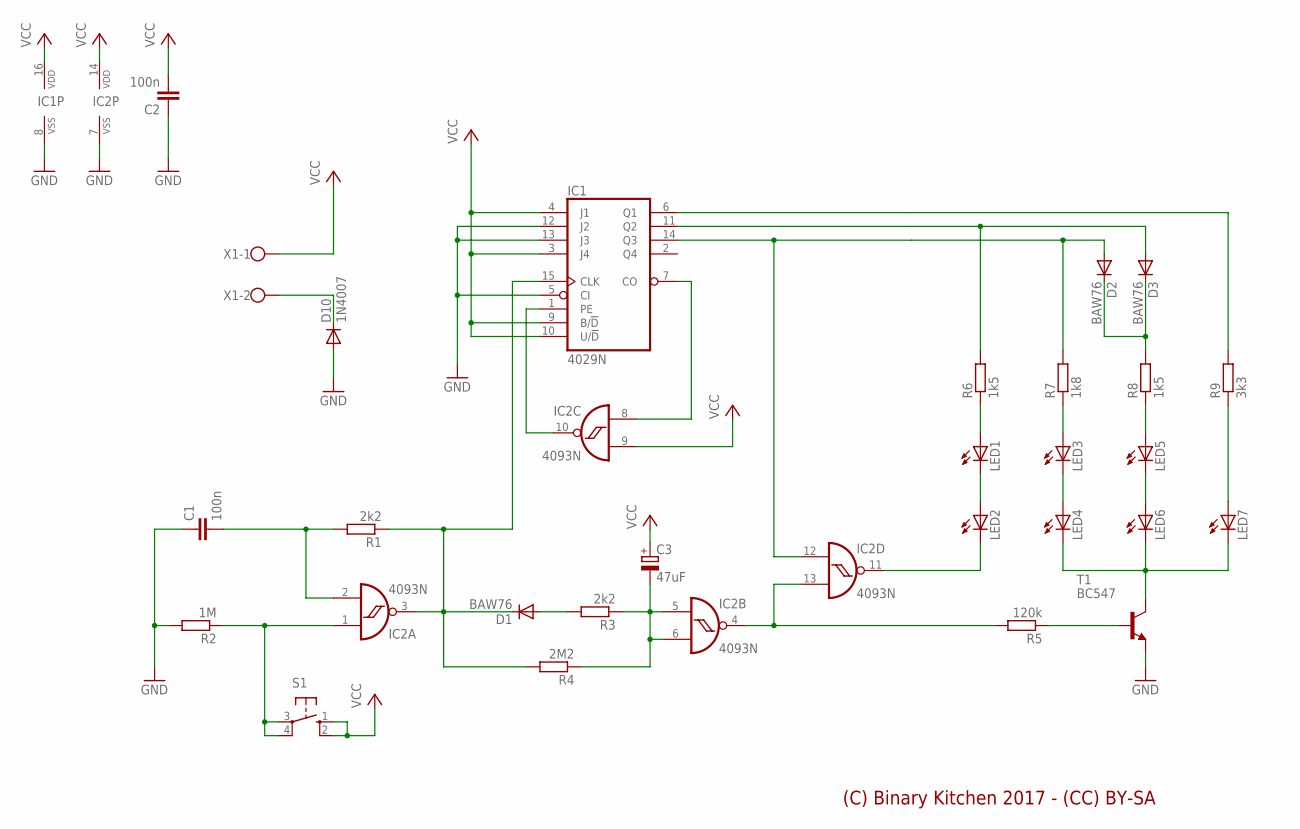
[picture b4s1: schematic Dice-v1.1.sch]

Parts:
C1, C2: 100n; C050-025X075
C3: 47uF; E2-5
D1, D2, D3: BAW76; DO35-10
D10: 1N4007; DO41-10
IC1: 4029N; DIL16
IC2: 4093N; DIL14
LED1, LED2, LED3, LED4, LED5, LED6, LED7: LED5MM
R1, R3: 2k2; 0207/7
R2: 1M; 0207/7
R4: 2M2; 0207/7
R5: 120k; 0207/7
R6, R8: 1k5; 0207/7
R7: 1k8; 0207/7
R9: 3k3; 0207/7
S1: 10-XX; B3F-10XX
T1: BC547; TO92
X1: W237-102

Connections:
GND: C1.1, C2.1, D10.A, IC1.5 (CI), IC1.8 (VSS), IC1.12 (J2), IC1.13 (J3), IC2.7 (VSS), R2.2, T1.1 (E)
unnamed: C1.2, IC2.2 (I1), R1.2
unnamed: IC2.11 (O), LED2.K (C)
unnamed: LED1.K (C), LED2.A
unnamed: LED4.K (C), LED6.K (C), LED7.K (C), T1.3 (C)
unnamed: LED3.K (C), LED4.A
unnamed: LED5.K (C), LED6.A
unnamed: LED1.A, R6.1
unnamed: LED3.A, R7.1
unnamed: LED5.A, R8.1
unnamed: LED7.A, R9.1
unnamed: R5.1, T1.2 (B)
unnamed: IC2.4 (O), IC2.13 (I1), R5.2
unnamed: IC1.1 (PE), IC2.10 (O)
unnamed: IC1.7 (CO), IC2.8 (I0)
unnamed: C3.-, IC2.5 (I0), IC2.6 (I1), R3.1, R4.1
unnamed: D1.A, R3.2
unnamed: D1.C, IC1.15 (CLK), IC2.3 (O), R1.1, R4.2
unnamed: D2.C, D3.C, R8.2
unnamed: D2.A, IC1.14 (Q3), IC2.12 (I0), R7.2
unnamed: D3.A, IC1.11 (Q2), R6.2
unnamed: IC1.6 (Q1), R9.2
unnamed: D10.C, X1.2
unnamed: IC2.1 (I0), R2.1, S1.3, S1.4 (P1)
VCC: C2.2, C3.+, IC1.3 (J4), IC1.4 (J1), IC1.9 (B/!D), IC1.10 (U/!D), IC1.16 (VDD), IC2.9 (I1), IC2.14 (VDD), S1.1 (S), S1.2 (S1), X1.1

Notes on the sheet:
(C) Binary Kitchen 2017 - (CC) BY-SA

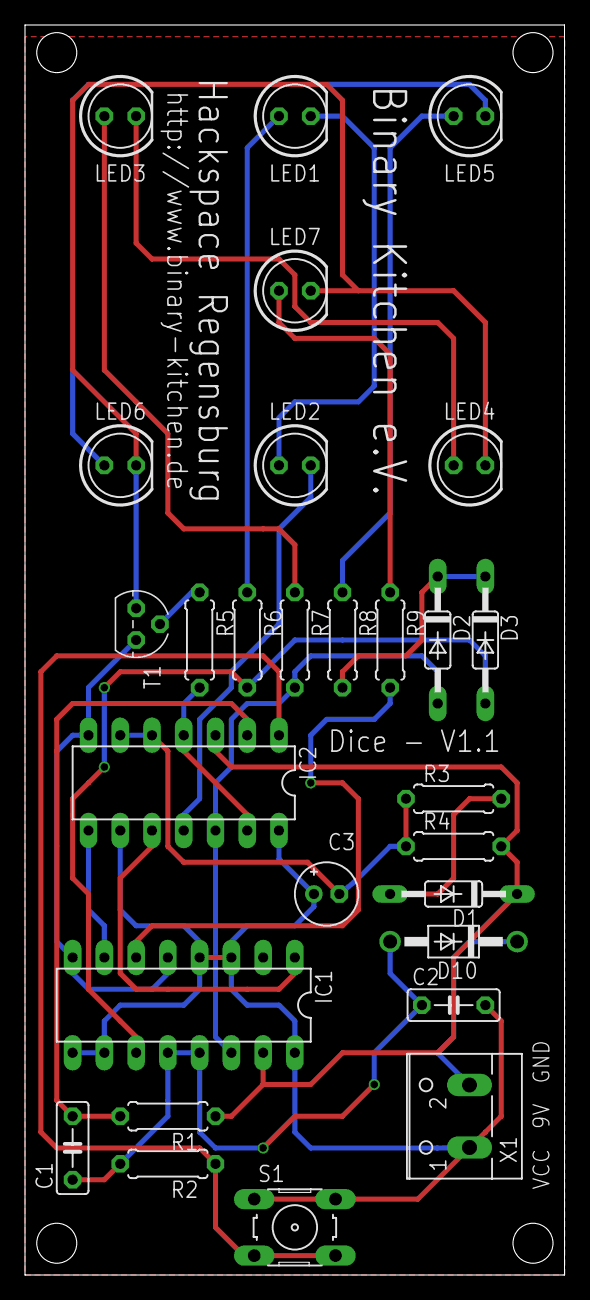
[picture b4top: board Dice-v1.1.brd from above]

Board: 2 copper layers, 43.2 x 100.0 mm, 28 parts (0 on the bottom side), 25 nets.

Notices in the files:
parts and their libraries:
SparkFun-Batteries: Licensing: Creative Commons ShareAlike 4.0 International - https://creativecommons.org/licenses/by-sa/4.0
